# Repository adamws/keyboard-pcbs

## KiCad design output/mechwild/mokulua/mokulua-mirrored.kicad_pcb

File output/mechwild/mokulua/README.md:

## mechwild/mokulua/mokulua-mirrored

[layout](mokulua-mirrored-kle.json) - [PCB](mokulua-mirrored.kicad_pcb)

{:loading="lazy"}

[Open in keyboard-layout-editor](http://www.keyboard-layout-editor.com/##@@_x:3.22&y:1.05&c=#777777;&=0,0%0A%0A%0A3,0&_c=#cccccc;&=0,1%0A%0A%0A3,0&_x:13.03&c=#aaaaaa&w:2;&=6,1%0A%0A%0A1,0;&@_x:2.97&w:1.5;&=1,0&_c=#cccccc;&=1,1&_x:12.53;&=7,1&_c=#aaaaaa&w:1.5;&=7,0;&@_x:2.87&w:1.75;&=2,0&_c=#cccccc;&=2,1&_x:12.23;&=8,1&_c=#777777&w:1.75;&=8,0;&@_x:2.72&c=#aaaaaa&w:2.25;&=3,0%0A%0A%0A0,0&_c=#cccccc;&=3,2&_x:11.53;&=9,2&_c=#777777;&=9,1%0A%0A%0A2,0&_c=#aaaaaa&w:1.25;&=9,0%0A%0A%0A2,0;&@_x:2.97;&=4,0&=4,1&=4,2&_x:11.53&c=#777777;&=10,2&=10,1&=10,0;&@_x:10.15&y:-0.95;&=5,2%0A%0A%0A4,0&_x:1.25;&=11,2%0A%0A%0A5,0;&@_x:9.82&c=#aaaaaa;&=5,0&_x:1.91;&=11,0;&@_r:10&rx:2.75&ry:3.75&x:2.25&y:-3.25&c=#cccccc;&=0,2&=0,3&=0,4&=0,5&=5,5;&@_x:2.75;&=1,2&=1,3&=1,4&=1,5&=5,4;&@_x:3.0;&=2,2&=2,3&=2,4&=2,5&=5,3;&@_x:3.5;&=3,3&=3,4&=3,5&=5,1;&@_x:3.75&c=#aaaaaa&w:1.25;&=4,3;&@_r:75&rx:10.5&ry:5.75&x:1.0&y:-5.25&c=#cccccc&w:1.5;&=10,4;&@_x:1.0&w:1.5;&=10,5;&@_r:-75&rx:0&ry:5&x:0.1&y:7.5&w:1.5;&=4,4;&@_x:0.1&w:1.5;&=4,5;&@_r:-10&rx:12&ry:4.25&x:1.5&y:-2.25;&=11,5&=6,5&=6,4&=6,3&=6,2;&@_x:1;&=11,4&=7,5&=7,4&=7,3&=7,2;&@_x:0.75;&=11,3&=8,5&=8,4&=8,3&=8,2;&@_x:1.25;&=11,1&=9,5&=9,4&=9,3;&@_x:3.75&c=#aaaaaa&w:1.25;&=10,3;&@_r:0&rx:0&ry:0&y:1.05&c=#777777&w:2;&=0,1%0A%0A%0A3,1&_x:19.0&c=#cccccc;&=6,1%0A%0A%0A1,1&_c=#aaaaaa;&=6,0%0A%0A%0A1,1;&@_y:2.0&w:1.25;&=3,0%0A%0A%0A0,1&_c=#cccccc;&=3,1%0A%0A%0A0,1&_x:18.75&c=#aaaaaa&w:2.25;&=9,0%0A%0A%0A2,1;&@_y:0.05&c=#777777;&=5,2%0A%0A%0A4,1%0A%0A%0A%0A%0A%0Ae0&_x:21.25;&=11,2%0A%0A%0A5,1%0A%0A%0A%0A%0A%0Ae0)

{:loading="lazy"}

## mechwild/mokulua/mokulua-standard

[layout](mokulua-standard-kle.json) - [PCB](mokulua-standard.kicad_pcb)

{:loading="lazy"}

[Open in keyboard-layout-editor](http://www.keyboard-layout-editor.com/##@@_x:3.22&y:1.05&c=#777777;&=0,0%0A%0A%0A3,0&_c=#cccccc;&=0,1%0A%0A%0A3,0&_x:12.53&c=#aaaaaa&w:2;&=6,5%0A%0A%0A1,0;&@_x:2.97&w:1.5;&=1,0&_c=#cccccc;&=1,1&_x:12.03;&=7,4&_c=#aaaaaa&w:1.5;&=7,5;&@_x:2.87&w:1.75;&=2,0&_c=#cccccc;&=2,1&_x:12.23;&=8,4&_c=#777777&w:1.75;&=8,5;&@_x:2.72&c=#aaaaaa&w:2.25;&=3,0%0A%0A%0A0,0&_c=#cccccc;&=3,2&_x:11.53;&=9,3&_c=#777777;&=9,4%0A%0A%0A2,0&_c=#aaaaaa&w:1.25;&=9,5%0A%0A%0A2,0;&@_x:2.97;&=4,0&=4,1&=4,2&_x:11.53&c=#777777;&=10,3&=10,4&=10,5;&@_x:10.15&y:-0.95;&=5,2%0A%0A%0A4,0&_x:1.25;&=11,3%0A%0A%0A5,0;&@_x:9.82&c=#aaaaaa;&=5,0&_x:1.91;&=11,4;&@_r:10&rx:2.75&ry:3.75&x:2.25&y:-3.25&c=#cccccc;&=0,2&=0,3&=0,4&=0,5&=5,5;&@_x:2.75;&=1,2&=1,3&=1,4&=1,5&=5,4;&@_x:3.0;&=2,2&=2,3&=2,4&=2,5&=5,3;&@_x:3.5;&=3,3&=3,4&=3,5&=5,1;&@_x:3.75&c=#aaaaaa&w:1.25;&=4,3;&@_r:75&rx:10.5&ry:5.75&x:1.0&y:-5.25&c=#cccccc&w:1.5;&=10,1;&@_x:1.0&w:1.5;&=10,0;&@_r:-75&rx:0&ry:5&x:0.1&y:7.5&w:1.5;&=4,4;&@_x:0.1&w:1.5;&=4,5;&@_r:-10&rx:12&ry:4.25&x:1&y:-2.25;&=11,0&=6,0&=6,1&=6,2&=6,3;&@_x:1.5;&=7,0&=7,1&=7,2&=7,3;&@_x:0.75;&=11,1&=8,0&=8,1&=8,2&=8,3;&@_x:1.25;&=11,2&=9,0&=9,1&=9,2;&@_x:3.75&c=#aaaaaa&w:1.25;&=10,2;&@_r:0&rx:0&ry:0&y:1.05&c=#777777&w:2;&=0,1%0A%0A%0A3,1&_x:19.0&c=#cccccc;&=6,4%0A%0A%0A1,1&_c=#aaaaaa;&=6,5%0A%0A%0A1,1;&@_y:2.0&w:1.25;&=3,0%0A%0A%0A0,1&_c=#cccccc;&=3,1%0A%0A%0A0,1&_x:18.75&c=#aaaaaa&w:2.25;&=9,5%0A%0A%0A2,1;&@_y:0.05&c=#777777;&=5,2%0A%0A%0A4,1%0A%0A%0A%0A%0A%0Ae0&_x:21.25;&=11,3%0A%0A%0A5,1%0A%0A%0A%0A%0A%0Ae0)

{:loading="lazy"}

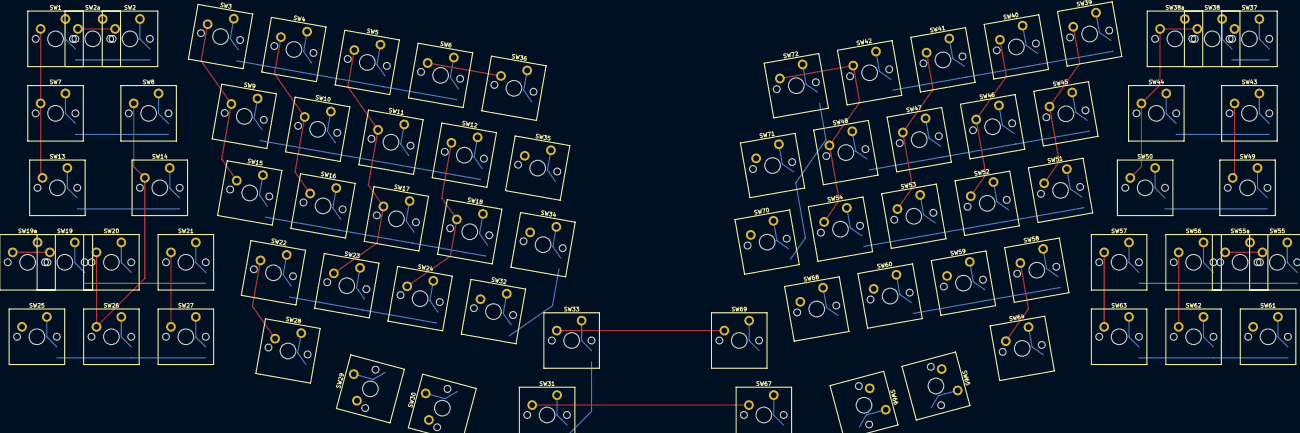
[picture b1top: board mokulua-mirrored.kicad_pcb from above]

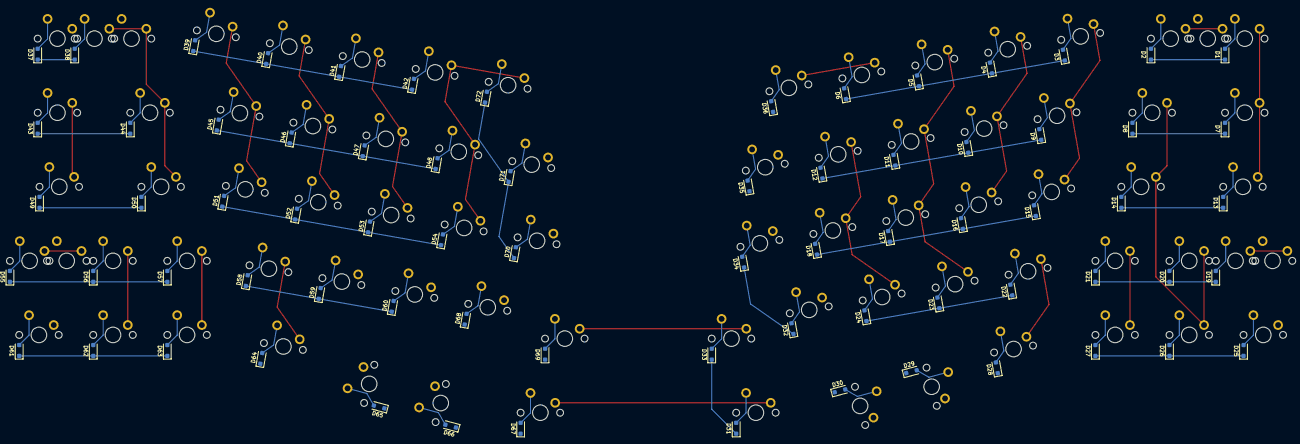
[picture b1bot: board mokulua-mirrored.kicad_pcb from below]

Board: 2 copper layers, 148 parts (72 on the bottom side), 90 nets.

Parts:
D1, D2, D3, D4, D5, D6, D7, D8, D9, D10, D11, D12, D13, D14, D15, D16, D17, D18, D19, D20, D21, D22, D23, D24, D25, D26, D27, D28, D29, D30, D31, D32, D33, D34, D35, D36, D37, D38, D39, D40, D41, D42, D43, D44, D45, D46, D47, D48, D49, D50, D51, D52, D53, D54, D55, D56, D57, D58, D59, D60, D61, D62, D63, D64, D65, D66, D67, D68, D69, D70, D71, D72: D_SOD-123F
SW1, SW2, SW2a, SW3, SW4, SW5, SW6, SW7, SW8, SW9, SW10, SW11, SW12, SW13, SW14, SW15, SW16, SW17, SW18, SW19, SW19a, SW20, SW21, SW22, SW23, SW24, SW25, SW26, SW27, SW28, SW29, SW30, SW31, SW32, SW33, SW34, SW35, SW36, SW37, SW38, SW38a, SW39, SW40, SW41, SW42, SW43, SW44, SW45, SW46, SW47, SW48, SW49, SW50, SW51, SW52, SW53, SW54, SW55, SW55a, SW56, SW57, SW58, SW59, SW60, SW61, SW62, SW63, SW64, SW65, SW66, SW67, SW68, SW69, SW70, SW71, SW72: SW_Cherry_MX_PCB_1.00u

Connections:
COL0: SW1.1, SW7.1, SW13.1, SW19.1, SW19a.1, SW25.1, SW31.1, SW37.1, SW43.1, SW49.1, SW55.1, SW55a.1, SW61.1, SW67.1
COL1: SW2.1, SW2a.1, SW8.1, SW14.1, SW20.1, SW26.1, SW32.1, SW38.1, SW38a.1, SW44.1, SW50.1, SW56.1, SW62.1, SW68.1
COL2: SW3.1, SW9.1, SW15.1, SW21.1, SW27.1, SW33.1, SW39.1, SW45.1, SW51.1, SW57.1, SW63.1, SW69.1
COL3: SW4.1, SW10.1, SW16.1, SW22.1, SW28.1, SW34.1, SW40.1, SW46.1, SW52.1, SW58.1, SW64.1, SW70.1
COL4: SW5.1, SW11.1, SW17.1, SW23.1, SW29.1, SW35.1, SW41.1, SW47.1, SW53.1, SW59.1, SW65.1, SW71.1
COL5: SW6.1, SW12.1, SW18.1, SW24.1, SW30.1, SW36.1, SW42.1, SW48.1, SW54.1, SW60.1, SW66.1, SW72.1
unnamed: D1.2, SW1.2
unnamed: D2.2, SW2.2, SW2a.2
unnamed: D3.2, SW3.2
unnamed: D4.2, SW4.2
unnamed: D5.2, SW5.2
unnamed: D6.2, SW6.2
unnamed: D7.2, SW7.2
unnamed: D8.2, SW8.2
unnamed: D9.2, SW9.2
unnamed: D10.2, SW10.2
unnamed: D11.2, SW11.2
unnamed: D12.2, SW12.2
unnamed: D13.2, SW13.2
unnamed: D14.2, SW14.2
unnamed: D15.2, SW15.2
unnamed: D16.2, SW16.2
unnamed: D17.2, SW17.2
unnamed: D18.2, SW18.2
unnamed: D19.2, SW19.2, SW19a.2
unnamed: D20.2, SW20.2
unnamed: D21.2, SW21.2
unnamed: D22.2, SW22.2
unnamed: D23.2, SW23.2
unnamed: D24.2, SW24.2
unnamed: D25.2, SW25.2
unnamed: D26.2, SW26.2
unnamed: D27.2, SW27.2
unnamed: D28.2, SW28.2
unnamed: D29.2, SW29.2
unnamed: D30.2, SW30.2
unnamed: D31.2, SW31.2
unnamed: D32.2, SW32.2
unnamed: D33.2, SW33.2
unnamed: D34.2, SW34.2
unnamed: D35.2, SW35.2
unnamed: D36.2, SW36.2
unnamed: D37.2, SW37.2
unnamed: D38.2, SW38.2, SW38a.2
unnamed: D39.2, SW39.2
unnamed: D40.2, SW40.2
unnamed: D41.2, SW41.2
unnamed: D42.2, SW42.2
unnamed: D43.2, SW43.2
unnamed: D44.2, SW44.2
unnamed: D45.2, SW45.2
unnamed: D46.2, SW46.2
unnamed: D47.2, SW47.2
unnamed: D48.2, SW48.2
unnamed: D49.2, SW49.2
unnamed: D50.2, SW50.2
unnamed: D51.2, SW51.2
unnamed: D52.2, SW52.2
unnamed: D53.2, SW53.2
unnamed: D54.2, SW54.2
unnamed: D55.2, SW55.2, SW55a.2
unnamed: D56.2, SW56.2
unnamed: D57.2, SW57.2
unnamed: D58.2, SW58.2
unnamed: D59.2, SW59.2
unnamed: D60.2, SW60.2
unnamed: D61.2, SW61.2
unnamed: D62.2, SW62.2
unnamed: D63.2, SW63.2
unnamed: D64.2, SW64.2
unnamed: D65.2, SW65.2
unnamed: D66.2, SW66.2
unnamed: D67.2, SW67.2
unnamed: D68.2, SW68.2
unnamed: D69.2, SW69.2
unnamed: D70.2, SW70.2
unnamed: D71.2, SW71.2
unnamed: D72.2, SW72.2
ROW0: D1.1, D2.1, D3.1, D4.1, D5.1, D6.1
ROW1: D7.1, D8.1, D9.1, D10.1, D11.1, D12.1
ROW2: D13.1, D14.1, D15.1, D16.1, D17.1, D18.1
ROW3: D19.1, D20.1, D21.1, D22.1, D23.1, D24.1
ROW4: D25.1, D26.1, D27.1, D28.1, D29.1, D30.1
ROW5: D31.1, D32.1, D33.1, D34.1, D35.1, D36.1
ROW6: D37.1, D38.1, D39.1, D40.1, D41.1, D42.1
ROW7: D43.1, D44.1, D45.1, D46.1, D47.1, D48.1
ROW8: D49.1, D50.1, D51.1, D52.1, D53.1, D54.1
ROW9: D55.1, D56.1, D57.1, D58.1, D59.1, D60.1
ROW10: D61.1, D62.1, D63.1, D64.1, D65.1, D66.1
ROW11: D67.1, D68.1, D69.1, D70.1, D71.1, D72.1

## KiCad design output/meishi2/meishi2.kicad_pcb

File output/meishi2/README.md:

## meishi2/meishi2

[layout](meishi2-kle.json) - [PCB](meishi2.kicad_pcb)

{:loading="lazy"}

[Open in keyboard-layout-editor](http://www.keyboard-layout-editor.com/##@@=0,0&=0,1&=1,0&=1,1)

{:loading="lazy"}

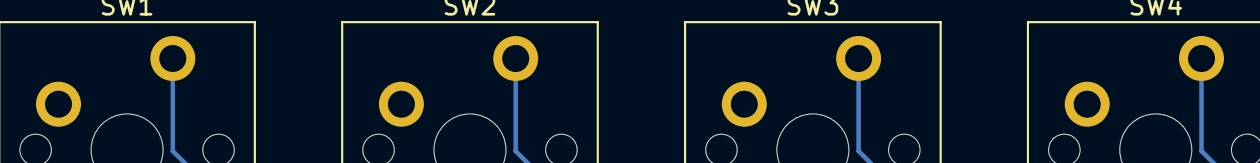
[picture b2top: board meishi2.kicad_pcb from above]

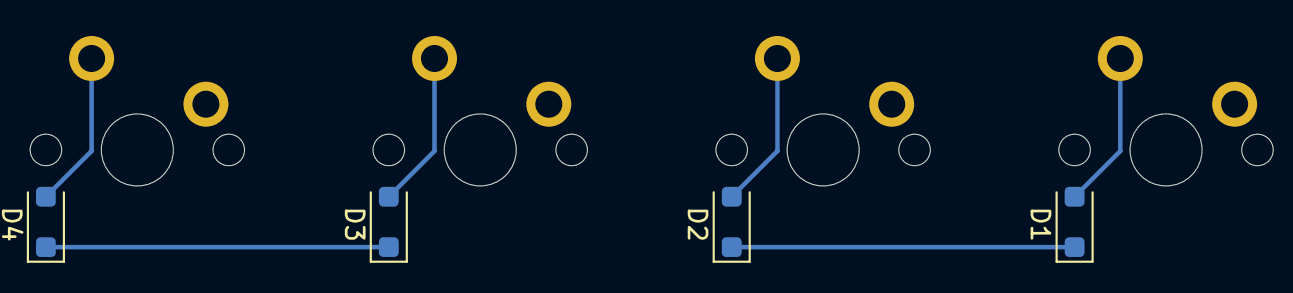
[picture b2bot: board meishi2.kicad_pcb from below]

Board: 2 copper layers, 8 parts (4 on the bottom side), 8 nets.

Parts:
D1, D2, D3, D4: D_SOD-123F
SW1, SW2, SW3, SW4: SW_Cherry_MX_PCB_1.00u

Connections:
COL0: SW1.1, SW3.1
COL1: SW2.1, SW4.1
unnamed: D1.2, SW1.2
unnamed: D2.2, SW2.2
unnamed: D3.2, SW3.2
unnamed: D4.2, SW4.2
ROW0: D1.1, D2.1
ROW1: D3.1, D4.1
